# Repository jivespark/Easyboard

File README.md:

# Easyboard
A devboard built for prototyping. It is built to be easy to make quick circuits and test out firmware easily by just plugging this into a laptop and connecting some components. It has a male USB-A connector on the end to make it easy to use without any wires. I built this because I wanted to have a microcontroller that I can just quickly and easily prototye with, and test stuff out for other projects.

Project render:

PCB:  

Schematic:

BOM:
|Name             |Purpose                |Quantity|Total Cost (USD)|Link              |Distributor|Comment                                                                                   |
|-----------------|-----------------------|--------|----------------|------------------|-----------|------------------------------------------------------------------------------------------|
|PCB with assembly|The PCBA for the design|1       |45.28           |https://jlcpcb.com|JLCPCB     |I couldn't include the proper link, since JLCPCB orders are custom, and don't have a link.|

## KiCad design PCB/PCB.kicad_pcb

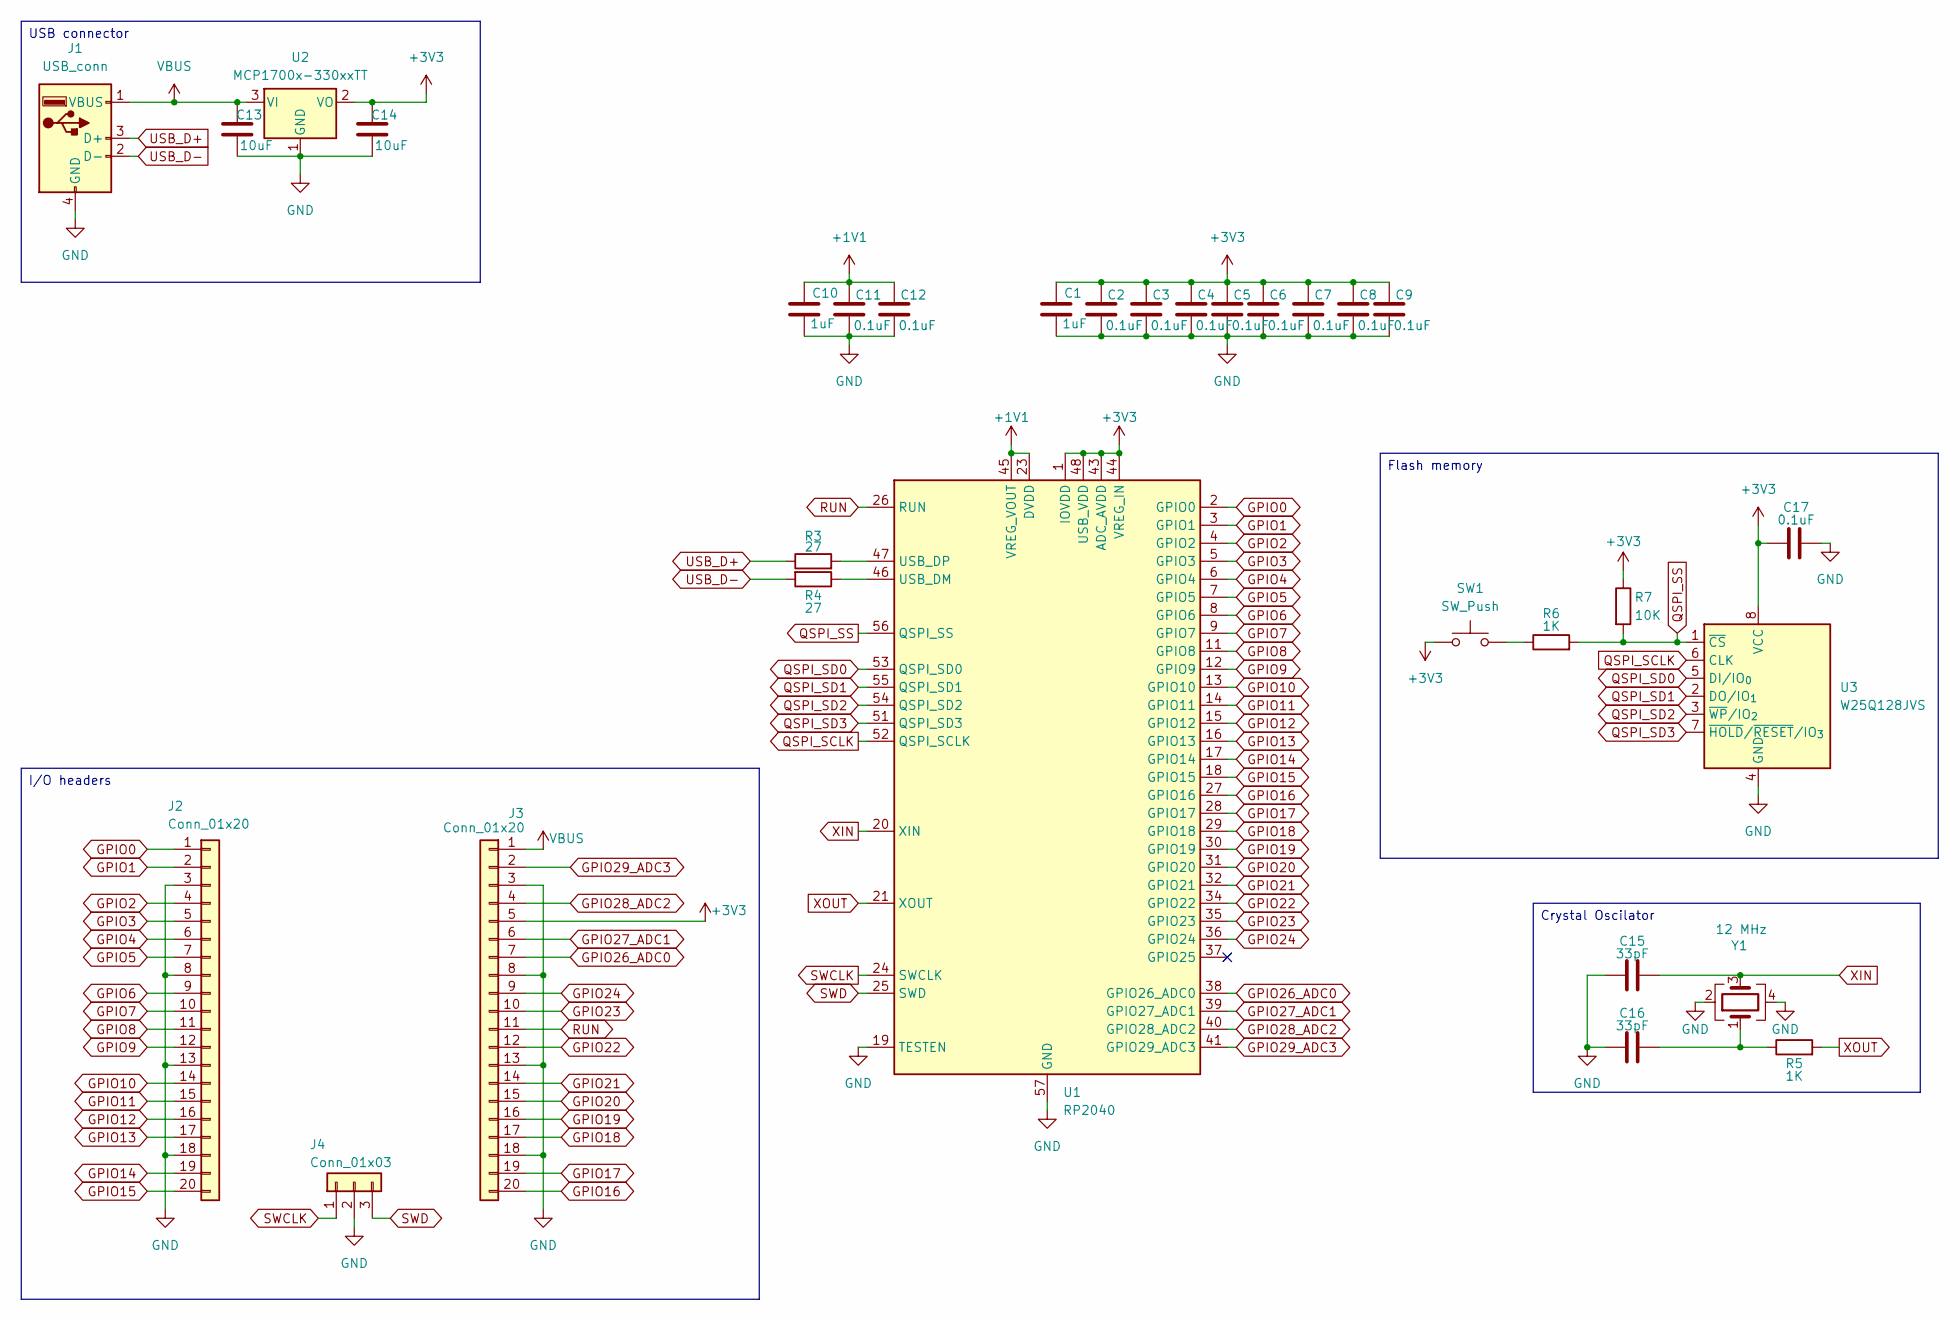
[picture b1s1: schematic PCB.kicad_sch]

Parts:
C1, C10: 1uF; C_0402_1005Metric
C2, C3, C4, C5, C6, C7, C8, C9, C11, C12, C17: 0.1uF; C_0402_1005Metric
C13, C14: 10uF; C_0603_1608Metric
C15, C16: 33pF; C_0402_1005Metric
J1: USB_conn; USB_A_PCB_Edge_receptacle
J2, J3: Conn_01x20; PinHeader_1x20_P2.54mm_Vertical
J4: Conn_01x03; PinHeader_1x03_P2.54mm_Vertical
R3, R4: 27; R_0402_1005Metric
R5, R6: 1K; R_0402_1005Metric
R7: 10K; R_0402_1005Metric
SW1: SW_Push; SW_Push_SPST_NO_Alps_SKRK
U1: RP2040; QFN-56-1EP_7x7mm_P0.4mm_EP3.2x3.2mm
U2: MCP1700x-330xxTT; SOT-23
U3: W25Q128JVS; Winbond_USON-8-1EP_3x2mm_P0.5mm_EP0.2x1.6mm
Y1: 12 MHz; Crystal_SMD_3225-4Pin_3.2x2.5mm

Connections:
+1V1: C10.1, C11.1, C12.1, U1.23 (DVDD), U1.45 (VREG_VOUT), U1.50 (DVDD)
+3V3: C1.1, C2.1, C3.1, C4.1, C5.1, C6.1, C7.1, C8.1, C9.1, C14.1, C17.1, J3.5, R7.1, SW1.1, U1.1 (IOVDD), U1.10 (IOVDD), U1.22 (IOVDD), U1.33 (IOVDD), U1.42 (IOVDD), U1.43 (ADC_AVDD), U1.44 (VREG_IN), U1.48 (USB_VDD), U1.49 (IOVDD), U2.2 (VO), U3.8 (VCC)
GND: C1.2, C2.2, C3.2, C4.2, C5.2, C6.2, C7.2, C8.2, C9.2, C10.2, C11.2, C12.2, C13.2, C14.2, C15.1, C16.1, C17.2, J1.4 (GND), J2.3, J2.8, J2.13, J2.18, J3.3, J3.8, J3.13, J3.18, J4.2, U1.19 (TESTEN), U1.57 (GND), U2.1 (GND), U3.4 (GND), Y1.2, Y1.4
GPIO0: J2.1, U1.2 (GPIO0)
GPIO1: J2.2, U1.3 (GPIO1)
GPIO2: J2.4, U1.4 (GPIO2)
GPIO3: J2.5, U1.5 (GPIO3)
GPIO4: J2.6, U1.6 (GPIO4)
GPIO5: J2.7, U1.7 (GPIO5)
GPIO6: J2.9, U1.8 (GPIO6)
GPIO7: J2.10, U1.9 (GPIO7)
GPIO8: J2.11, U1.11 (GPIO8)
GPIO9: J2.12, U1.12 (GPIO9)
GPIO10: J2.14, U1.13 (GPIO10)
GPIO11: J2.15, U1.14 (GPIO11)
GPIO12: J2.16, U1.15 (GPIO12)
GPIO13: J2.17, U1.16 (GPIO13)
GPIO14: J2.19, U1.17 (GPIO14)
GPIO15: J2.20, U1.18 (GPIO15)
GPIO16: J3.20, U1.27 (GPIO16)
GPIO17: J3.19, U1.28 (GPIO17)
GPIO18: J3.17, U1.29 (GPIO18)
GPIO19: J3.16, U1.30 (GPIO19)
GPIO20: J3.15, U1.31 (GPIO20)
GPIO21: J3.14, U1.32 (GPIO21)
GPIO22: J3.12, U1.34 (GPIO22)
GPIO23: J3.10, U1.35 (GPIO23)
GPIO24: J3.9, U1.36 (GPIO24)
GPIO26_ADC0: J3.7, U1.38 (GPIO26_ADC0)
GPIO27_ADC1: J3.6, U1.39 (GPIO27_ADC1)
GPIO28_ADC2: J3.4, U1.40 (GPIO28_ADC2)
GPIO29_ADC3: J3.2, U1.41 (GPIO29_ADC3)
unnamed: C16.2, R5.1, Y1.1
unnamed: R6.1, SW1.2
unnamed: R4.1, U1.46 (USB_DM)
unnamed: R3.2, U1.47 (USB_DP)
QSPI_SCLK: U1.52 (QSPI_SCLK), U3.6 (CLK)
QSPI_SD0: U1.53 (QSPI_SD0), U3.5 (DI/IO_{0})
QSPI_SD1: U1.55 (QSPI_SD1), U3.2 (DO/IO_{1})
QSPI_SD2: U1.54 (QSPI_SD2), U3.3 (~WP/IO_{2})
QSPI_SD3: U1.51 (QSPI_SD3), U3.7 (~HOLD/~RESET/IO_{3})
QSPI_SS: R6.2, R7.2, U1.56 (QSPI_SS), U3.1 (~CS)
RUN: J3.11, U1.26 (RUN)
SWCLK: J4.1, U1.24 (SWCLK)
SWD: J4.3, U1.25 (SWD)
USB_D+: J1.3 (D+), R3.1
USB_D-: J1.2 (D-), R4.2
VBUS: C13.1, J1.1 (VBUS), J3.1, U2.3 (VI)
XIN: C15.2, U1.20 (XIN), Y1.3
XOUT: R5.2, U1.21 (XOUT)

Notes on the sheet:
I/O headers
USB connector
Crystal Oscilator
Flash memory

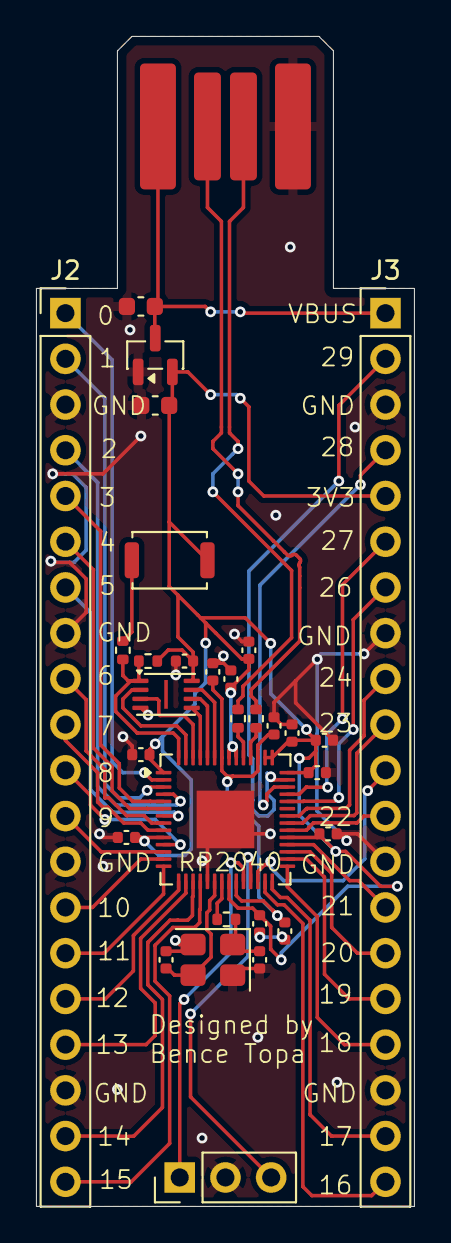
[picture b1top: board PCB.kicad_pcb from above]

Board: 2 copper layers, 21.0 x 65.0 mm, 31 parts (0 on the bottom side), 50 nets.

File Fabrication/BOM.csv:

Id,Designator,Footprint,Quantity,Comment,Supplier and ref
1,"C8,C3,C2,C5,C7,C17,C12,C9,C4,C11,C6",C_0402_1005Metric,11,0.1uF,
2,J1,USB_A_PCB_Edge_receptacle,1,USB_conn,
3,SW1,SW_Push_SPST_NO_Alps_SKRK,1,SW_Push,
4,J4,PinHeader_1x03_P2.54mm_Vertical,1,Conn_01x03,
5,"J2,J3",PinHeader_1x20_P2.54mm_Vertical,2,Conn_01x20,
6,"R6,R5",R_0402_1005Metric,2,1K,
7,U3,Winbond_USON-8-1EP_3x2mm_P0.5mm_EP0.2x1.6mm,1,W25Q128JVS,
8,"C15,C16",C_0402_1005Metric,2,33pF,
9,U2,SOT-23,1,MCP1700x-330xxTT,
10,"R3,R4",R_0402_1005Metric,2,27,
11,"C1,C10",C_0402_1005Metric,2,1uF,
12,Y1,Crystal_SMD_3225-4Pin_3.2x2.5mm,1,12 MHz,
13,"C14,C13",C_0603_1608Metric,2,10uF,
14,R7,R_0402_1005Metric,1,10K,
15,U1,QFN-56-1EP_7x7mm_P0.4mm_EP3.2x3.2mm,1,RP2040,

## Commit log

2026-04-23 Added PCB files
2026-04-23 Added fabrication files
2026-04-23 Added the BOM for Hack club
2026-04-23 Made the README
2026-04-23 Added project image
2026-04-23 Update README with project render
